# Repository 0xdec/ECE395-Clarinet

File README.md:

# Self-Playing Clarinet
A self-playing clarinet designed and built for ECE 395 - Advanced Digital Projects Laboratory - at the University of Illinois Urbana-Champaign.

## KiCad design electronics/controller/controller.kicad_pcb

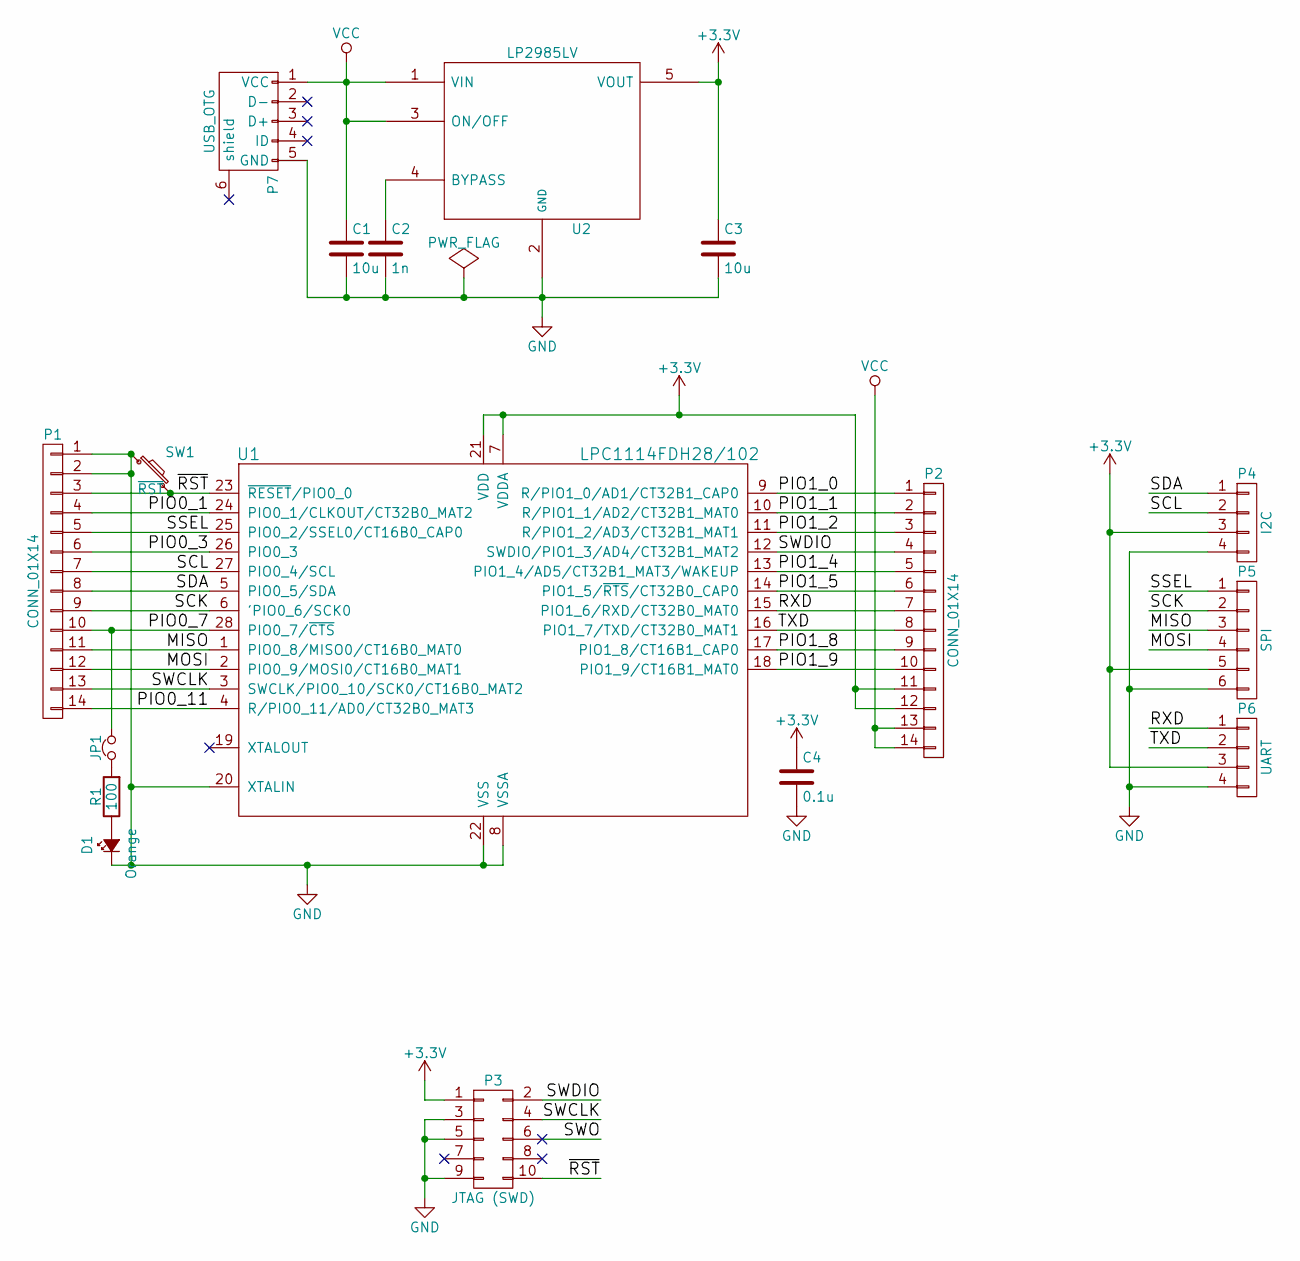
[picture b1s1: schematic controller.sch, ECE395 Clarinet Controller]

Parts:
C1, C3: 10u; C_0805
C2: 1n; C_0603
C4: 0.1u; C_0603
D1: Orange; LED-0603
JP1: Jumper_NC_Small
P1, P2: CONN_01X14; Socket_Strip_Straight_1x14
P3: JTAG (SWD); Pin_Header_Straight_2x05_Pitch1.27mm
P4: I2C; Connectors_JST_BM04B-SRSS-TB
P5: SPI; Connectors_JST_BM06B-SRSS-TB
P6: UART; Connectors_JST_BM04B-SRSS-TB
P7: USB_OTG; USB_Micro-B
R1: 100; R_0603
SW1: ~RST~; SW_SPST_EVQP7A
U1: LPC1114FDH28/102; TSSOP-28_4.4x9.7mm_Pitch0.65mm
U2: LP2985LV; SOT-23-5

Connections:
+3V3: C3.1, C4.1, P2.11, P2.12, P3.1, P4.3, P5.5, P6.3, U1.7 (VDDA), U1.21 (VDD), U2.5 (VOUT)
/MISO: P1.11, P5.3, U1.1 (PIO0_8/MISO0/CT16B0_MAT0)
/MOSI: P1.12, P5.4, U1.2 (PIO0_9/MOSI0/CT16B0_MAT1)
/PIO0_1: P1.4, U1.24 (PIO0_1/CLKOUT/CT32B0_MAT2)
/PIO0_3: P1.6, U1.26 (PIO0_3)
/PIO0_7: JP1.2, P1.10, U1.28 (PIO0_7/~CTS)
/PIO0_11: P1.14, U1.4 (R/PIO0_11/AD0/CT32B0_MAT3)
/PIO1_0: P2.1, U1.9 (R/PIO1_0/AD1/CT32B1_CAP0)
/PIO1_1: P2.2, U1.10 (R/PIO1_1/AD2/CT32B1_MAT0)
/PIO1_2: P2.3, U1.11 (R/PIO1_2/AD3/CT32B1_MAT1)
/PIO1_4: P2.5, U1.13 (PIO1_4/AD5/CT32B1_MAT3/WAKEUP)
/PIO1_5: P2.6, U1.14 (PIO1_5/~RTS~/CT32B0_CAP0)
/PIO1_8: P2.9, U1.17 (PIO1_8/CT16B1_CAP0)
/PIO1_9: P2.10, U1.18 (PIO1_9/CT16B1_MAT0)
/RXD: P2.7, P6.1, U1.15 (PIO1_6/RXD/CT32B0_MAT0)
/SCK: P1.9, P5.2, U1.6 ('PIO0_6/SCK0)
/SCL: P1.7, P4.2, U1.27 (PIO0_4/SCL)
/SDA: P1.8, P4.1, U1.5 (PIO0_5/SDA)
/SSEL: P1.5, P5.1, U1.25 (PIO0_2/SSEL0/CT16B0_CAP0)
/SWCLK: P1.13, P3.4, U1.3 (SWCLK/PIO0_10/SCK0/CT16B0_MAT2)
/SWDIO: P2.4, P3.2, U1.12 (SWDIO/PIO1_3/AD4/CT32B1_MAT2)
/SWO: P3.6
/TXD: P2.8, P6.2, U1.16 (PIO1_7/TXD/CT32B0_MAT1)
/~RST~: P1.3, P3.10, SW1.2, U1.23 (~RESET~/PIO0_0)
GND: C1.2, C2.2, C3.2, C4.2, D1.1 (K), P1.1, P1.2, P3.3, P3.5, P3.9, P4.4, P5.6, P6.4, P7.5 (GND), SW1.1, U1.8 (VSSA), U1.20 (XTALIN), U1.22 (VSS), U2.2 (GND)
unnamed: C2.1, U2.4 (BYPASS)
unnamed: D1.2 (A), R1.1
unnamed: JP1.1, R1.2
VCC: C1.1, P2.13, P2.14, P7.1 (VCC), U2.1 (VIN), U2.3 (ON/OFF)

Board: 2 copper layers, 16 parts (0 on the bottom side), 27 nets, no tracks yet.

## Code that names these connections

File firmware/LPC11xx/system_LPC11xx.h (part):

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       uint32_t RESERVED0[1];
  __IO uint32_t PIO2_0;                 /*!< Offset: 0x008 (R/W)  I/O configuration for pin PIO2_0/DTR/SSEL1 */
  __IO uint32_t RESET_PIO0_0;           /*!< Offset: 0x00C (R/W)  I/O configuration for pin RESET/PIO0_0  */
  __IO uint32_t PIO0_1;                 /*!< Offset: 0x010 (R/W)  I/O configuration for pin PIO0_1/CLKOUT/CT32B0_MAT2 */
  __IO uint32_t PIO1_8;                 /*!< Offset: 0x014 (R/W)  I/O configuration for pin PIO1_8/CT16B1_CAP0 */
       uint32_t RESERVED1[1];
  __IO uint32_t PIO0_2;                 /*!< Offset: 0x01C (R/W)  I/O configuration for pin PIO0_2/SSEL0/CT16B0_CAP0 */

  __IO uint32_t PIO2_7;                 /*!< Offset: 0x020 (R/W)  I/O configuration for pin PIO2_7 */
  __IO uint32_t PIO2_8;                 /*!< Offset: 0x024 (R/W)  I/O configuration for pin PIO2_8 */
  __IO uint32_t PIO2_1;                 /*!< Offset: 0x028 (R/W)  I/O configuration for pin PIO2_1/nDSR/SCK1 */
  __IO uint32_t PIO0_3;                 /*!< Offset: 0x02C (R/W)  I/O configuration for pin PIO0_3 */
  __IO uint32_t PIO0_4;                 /*!< Offset: 0x030 (R/W)  I/O configuration for pin PIO0_4/SCL */
  __IO uint32_t PIO0_5;                 /*!< Offset: 0x034 (R/W)  I/O configuration for pin PIO0_5/SDA */
  __IO uint32_t PIO1_9;                 /*!< Offset: 0x038 (R/W)  I/O configuration for pin PIO1_9/CT16B1_MAT0 */
  __IO uint32_t PIO3_4;                 /*!< Offset: 0x03C (R/W)  I/O configuration for pin PIO3_4 */

  __IO uint32_t PIO2_4;                 /*!< Offset: 0x040 (R/W)  I/O configuration for pin PIO2_4 */
  __IO uint32_t PIO2_5;                 /*!< Offset: 0x044 (R/W)  I/O configuration for pin PIO2_5 */
  __IO uint32_t PIO3_5;                 /*!< Offset: 0x048 (R/W)  I/O configuration for pin PIO3_5 */
  __IO uint32_t PIO0_6;                 /*!< Offset: 0x04C (R/W)  I/O configuration for pin PIO0_6/SCK0 */
  __IO uint32_t PIO0_7;                 /*!< Offset: 0x050 (R/W)  I/O configuration for pin PIO0_7/nCTS */
  __IO uint32_t PIO2_9;                 /*!< Offset: 0x054 (R/W)  I/O configuration for pin PIO2_9 */
  __IO uint32_t PIO2_10;                /*!< Offset: 0x058 (R/W)  I/O configuration for pin PIO2_10 */
  __IO uint32_t PIO2_2;                 /*!< Offset: 0x05C (R/W)  I/O configuration for pin PIO2_2/DCD/MISO1 */
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  __IO uint32_t SWCLK_PIO0_10;          /*!< Offset: 0x068 (R/W)  I/O configuration for pin SWCLK/PIO0_10/SCK0/CT16B0_MAT2 */
  __IO uint32_t PIO1_10;                /*!< Offset: 0x06C (R/W)  I/O configuration for pin PIO1_10/AD6/CT16B1_MAT1 */
  __IO uint32_t PIO2_11;                /*!< Offset: 0x070 (R/W)  I/O configuration for pin PIO2_11/SCK0 */
  __IO uint32_t R_PIO0_11;              /*!< Offset: 0x074 (R/W)  I/O configuration for pin TDI/PIO0_11/AD0/CT32B0_MAT3 */
  __IO uint32_t R_PIO1_0;               /*!< Offset: 0x078 (R/W)  I/O configuration for pin TMS/PIO1_0/AD1/CT32B1_CAP0 */
  __IO uint32_t R_PIO1_1;               /*!< Offset: 0x07C (R/W)  I/O configuration for pin TDO/PIO1_1/AD2/CT32B1_MAT0 */

  __IO uint32_t R_PIO1_2;               /*!< Offset: 0x080 (R/W)  I/O configuration for pin nTRST/PIO1_2/AD3/CT32B1_MAT1 */
  __IO uint32_t PIO3_0;                 /*!< Offset: 0x084 (R/W)  I/O configuration for pin PIO3_0/nDTR */
  __IO uint32_t PIO3_1;                 /*!< Offset: 0x088 (R/W)  I/O configuration for pin PIO3_1/nDSR */
  __IO uint32_t PIO2_3;                 /*!< Offset: 0x08C (R/W)  I/O configuration for pin PIO2_3/RI/MOSI1 */
  __IO uint32_t SWDIO_PIO1_3;           /*!< Offset: 0x090 (R/W)  I/O configuration for pin SWDIO/PIO1_3/AD4/CT32B1_MAT2 */
  __IO uint32_t PIO1_4;                 /*!< Offset: 0x094 (R/W)  I/O configuration for pin PIO1_4/AD5/CT32B1_MAT3 */
  __IO uint32_t PIO1_11;                /*!< Offset: 0x098 (R/W)  I/O configuration for pin PIO1_11/AD7 */
  __IO uint32_t PIO3_2;                 /*!< Offset: 0x09C (R/W)  I/O configuration for pin PIO3_2/nDCD */

  __IO uint32_t PIO1_5;                 /*!< Offset: 0x0A0 (R/W)  I/O configuration for pin PIO1_5/nRTS/CT32B0_CAP0 */
  __IO uint32_t PIO1_6;                 /*!< Offset: 0x0A4 (R/W)  I/O configuration for pin PIO1_6/RXD/CT32B0_MAT0 */
  __IO uint32_t PIO1_7;                 /*!< Offset: 0x0A8 (R/W)  I/O configuration for pin PIO1_7/TXD/CT32B0_MAT1 */
  __IO uint32_t PIO3_3;                 /*!< Offset: 0x0AC (R/W)  I/O configuration for pin PIO3_3/nRI */
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
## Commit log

2016-02-17 Restructure firmware directory
2016-02-17 Add notes on period vs duty cycle
2016-02-17 Add fixes for PWM timing
    Change the clock prescaler
2016-02-17 Fix inverted signal
2016-02-17 Add servo sweep test
2016-02-18 C doesn't have booleans
2016-02-24 Separate code into multiple files
2016-02-24 Add preliminary UART/MIDI functions
2016-02-24 Add UART interrupt (not yet implemented)
2016-02-24 Include standard libraries
2016-02-24 Remove unnecessary macros
2016-02-25 Move reference folder
2016-02-25 Make delay functions inline
2016-02-25 Make pwmPeriod static and volatile
2016-02-25 Move UART interrupt enable into initMIDI()
2016-02-25 Add MIDI interrupt handler
2016-02-25 Start writing noteOn and noteOff functions
2016-02-26 Add fingering generator
2016-02-26 gh-pages
2016-02-26 Get rid of ES6 dependence, add next/prev buttons
2016-02-26 Fixed Sweep
2016-02-27 Fix annoyingly-linked SVG bug
2016-02-27 Remove raw number from info view
2016-02-27 Remove fingering configurator from master
2016-02-27 Don't commit build products
2016-02-27 Remove reference + Eagle files
2016-02-27 Fix formatting
2016-02-27 Remove unused defines
2016-02-27 servoPos should take int
2016-02-27 Move firmware files back into firmware folder
2016-02-27 Fix PWM?
2016-02-27 Cleaning up shop
2016-02-27 Remove unnecessary CSS
2016-02-27 Fix C array
2016-02-27 Copy the previous note whenever a new one is created
2016-02-27 "Fix" some bad CSS positioning
    …hehehehe, get it?
2016-02-27 Add 3 octaves of clarinet fingerings
2016-02-27 Deprecate old version
2016-02-27 Rewrite using draft.js
2016-02-27 Change hosted domain name
2016-02-27 Servo position should be a signed int
2016-02-27 Remove hosted domain name
2016-02-27 Add link to new version
2016-02-27 Add missing semicolons
2016-02-27 Rearrange/beautify everything
2016-02-27 Add link to draft.js
2016-02-27 Add info
2016-02-27 More prettification
2016-02-27 Lowercase? Lowercase.
2016-03-02 Implement more MIDI, stop trying to use interrupts
2016-03-02 Change variable/function naming style
2016-03-02 Initial shift_out implementation
2016-03-02 LSB should be sent first
2016-03-02 Clean up comments
2016-03-02 Support note velocity (volume)
2016-03-02 Use servo for volume control
2016-03-02 Don't set registers to reserved values
2016-03-02 Implement SPI
2016-03-02 SPI prescaler has a minimum value of 2
2016-03-02 Use 16-bit SPI frames
2016-03-02 Fix range typo
    Clarinets can apparently play as low as an Eb, but we only want to use
    16 keys.
2016-03-02 Add note about note velocity
    Ha…pun-ey
2016-03-02 Rearrange timer initialization config settings
2016-03-02 Use SPI0 instead of SPI1
    The LPC1114FN28 only has SPI0 broken out to pins.
2016-03-02 Check if SPI transmit FIFO is full before transmitting
2016-03-02 Remove test servo code
2016-03-03 Beginnings of hardware abstraction
2016-03-03 First experiments in Kicad
2016-03-03 Add MIDI input and solenoid drive circuitry
2016-03-03 Rename hardware to electronics
2016-03-04 Add BJT solenoid driver
2016-03-04 Create separate solenoid driver
2016-03-08 Fix duplicate note
2016-03-08 Move shift registers to solenoid driver
2016-03-08 Fix creation of notes with all-open fingerings
2016-03-08 Working Keil
2016-03-08 Change SCK0 position to pin PIO0_6
2016-03-08 Fix typo
2016-03-09 Counting up
2016-03-09 Use soft tabs
2016-03-09 Move LPC11xx dependencies into LPC11xx
2016-03-09 Update pin definitions
2016-03-09 Add JTAG connector
2016-03-29 Move servo-related definitions into servo.h
2016-03-29 Add note_init()
2016-03-29 Handle transposition
2016-03-29 Make the MIDI channel configurable
2016-03-29 Remove SPI testing code, start testing MIDI
2016-03-29 C doesn't have default values
2016-03-29 Disallow channel 10 as it's reserved for percussion
2016-03-29 Fix switch statement
2016-03-29 Turns out I can't read
2016-03-30 Improve servo code
2016-03-31 Rewrite MIDI receiver
    - Fix bug with messages shorter than 3 bytes
    - Add preliminary System message handlers
2016-03-31 Add separate available UART data function
2016-03-31 Add clarinet stand model
2016-03-31 Move MIDI baud rate into definition
2016-03-31 Rename notes to note
2016-04-01 Clean up prototypes, fix some naming mistakes
2016-04-01 Prettify definitions
2016-04-01 Move baud rate calculation into MIDI_init()
2016-04-01 Add current note getter
2016-04-07 Add aftertouch/volume support
2016-04-09 Add pin headers, power regulator, and barrel jack
2016-04-10 Update microcontroller and regulator components
2016-04-10 Add NFET for reverse polarity protection
2016-04-12 Remove MIDI and solenoid circuits
2016-04-12 Create MIDI board
2016-04-12 Add LED on PIO0_7 (high-drive output)
2016-04-19 Layout MIDI_IN board
2016-04-19 Switch to LP2985 regulator, begin board layout
2016-05-05 More work on controller
2016-05-05 Start updating MIDI_IN board
    - add decoupling cap
    - change LED polarity
    - change 4-pin header to 3-pin
2016-05-05 Return part ID in system_init()
2016-05-05 Update gitignore
2016-05-05 Calculate actual pitch name
2016-05-05 Replace HTML entities for sharp/flat with symbols
2016-05-05 Properly transpose to clarinet key
2016-05-05 Fix getPitch()
2016-05-06 Update <head>
2016-05-09 Add comments
2016-05-09 Ignore dotfiles
2016-06-06 Move key_10 location
    Due to solenoid placement constraint, a different key had to be used
2016-06-06 Move key_13 location
    Due to solenoid placement constraint, a different key had to be used
2016-06-29 Add sub sheet for BJT driver
2016-10-17 Refactor interface drivers
    Rename send functions to transmit
2016-11-15 Clean up formatting
2016-11-15 Add I2C interface driver
2016-11-15 Add BMP180 pressure sensor driver
    Ported from SparkFun's BMP180 Arduino library
2016-11-26 Use static buffer size
2016-11-26 Rename internal functions
2016-11-26 Make internal state variables static
2016-12-01 Make BMP180 variables static/private
2016-12-01 Add PID library
2016-12-01 Use global variables instead of pointers
2016-12-03 Support different SPI frame sizes
2016-12-03 Boilerplate millis timer
2016-12-03 Remove servo usage
2016-12-03 Include <math.h>, improve comment/code formatting
2016-12-04 Rename PID variables
2016-12-04 Write pressure controller
2016-12-05 Fix broken C code
    - no pass-by-reference in C
    - private variables should not be static
    - static function declarations should be in .c file
2016-12-05 Use pin definitions instead of hard-coded pins
2016-12-05 Properly declare global variables
2016-12-06 Create and use global iocon register pointer array
2016-12-06 Use BIT(n) macro instead of BITn definitions
2016-12-06 Update pressure reading/PID every MIDI_receive
2016-12-06 Add core_cm0.h
2016-12-06 Clean up delay header
2016-12-06 Add system tick counter and time functions
2016-12-06 Remove time_millis() and time.c/h
2016-12-06 Add LPC11xx system header
2016-12-06 Remove duplicate header
2016-12-06 Add GPIO implementation
2016-12-06 Move lib files into sub directories
2016-12-06 Remove duplicate LPC11xx files
2016-12-06 Proper micros and millis implementation
2016-12-06 Update delay functions to use system timers
2016-12-06 Use uint32_t instead of unsigned long
2016-12-06 Use SystemCoreClock for baud rate calculation
2016-12-08 Fix header include locations
2016-12-10 Update Keil prefs
2016-12-10 Fix compile errors
2016-12-10 Add debug statements
2016-12-10 Fix state machine bug
    State 0x48 was being incorrectly handled by the 0x40 handler
2016-12-10 State 0x40 should read the first data byte
2016-12-10 Disable Fast-mode Plus I2C
2016-12-31 Add final report
2016-12-31 Add title and link to final report
2017-01-06 Add link to GitHub source
2017-01-06 Update repo name
2017-02-12 Fix indentation
2017-02-13 Add FontAwesome icon after external links
2017-05-05 Fix link to new version

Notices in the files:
firmware/LPC11xx/system_LPC11xx.h:
Copyright (C) 2009-2010 ARM Limited. All rights reserved.
